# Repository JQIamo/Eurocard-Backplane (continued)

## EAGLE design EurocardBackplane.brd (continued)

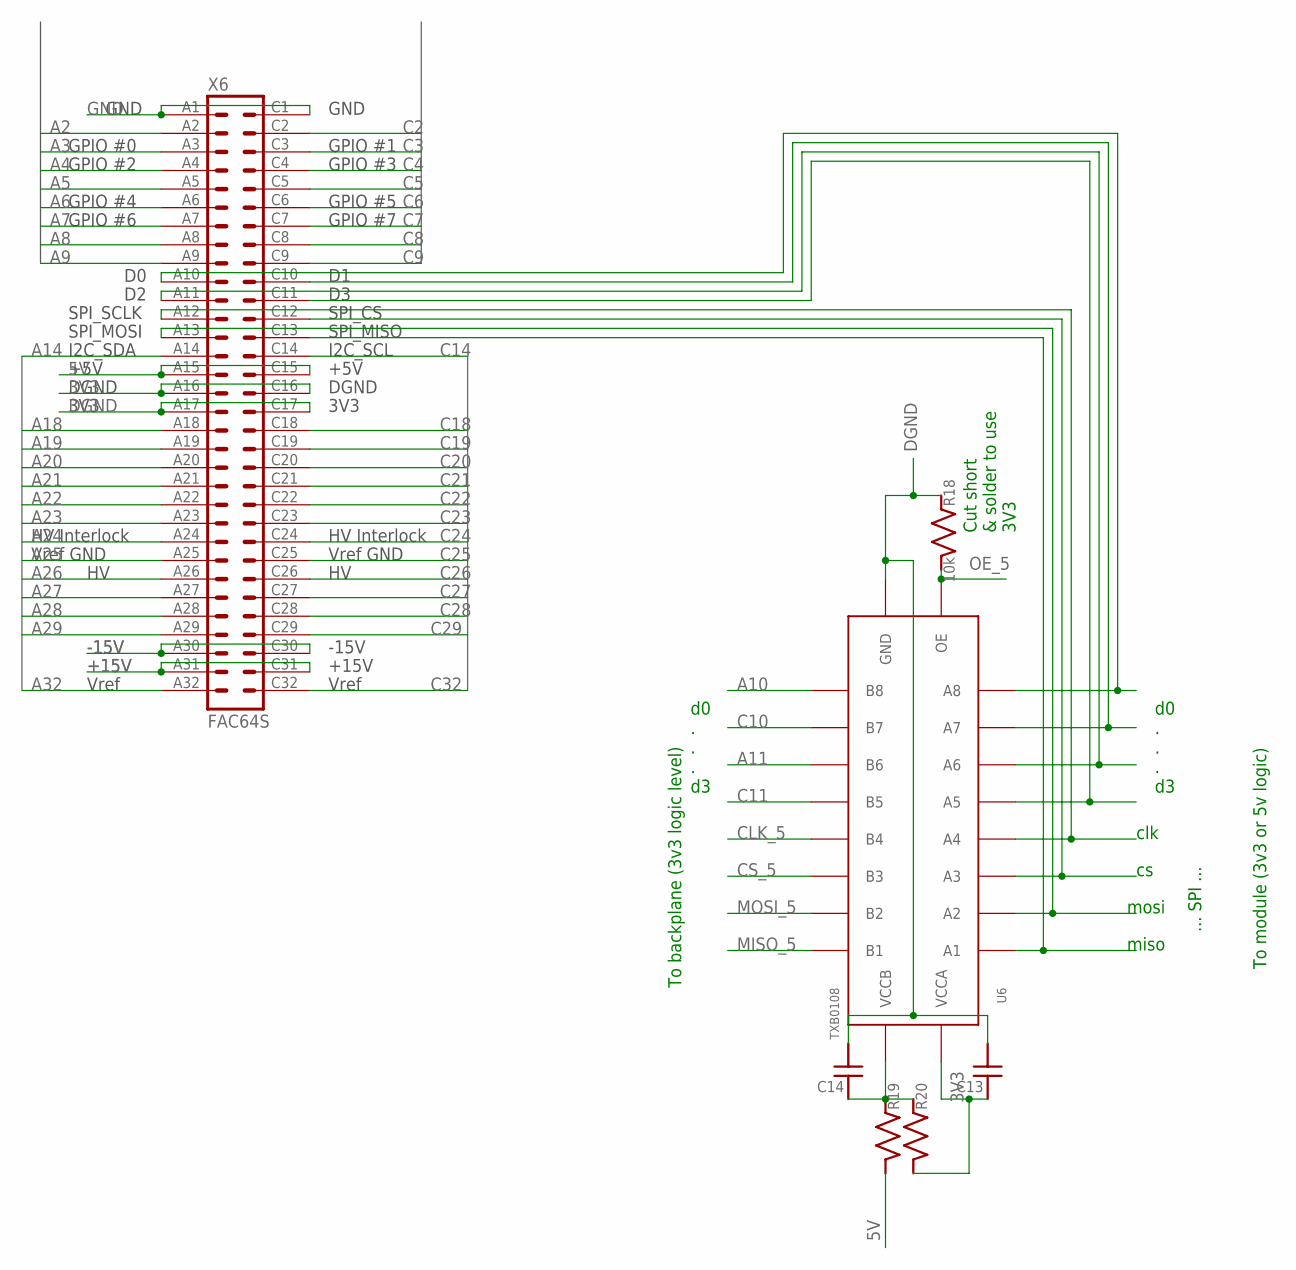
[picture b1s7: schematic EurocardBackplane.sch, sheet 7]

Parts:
C13, C14: C_MLCC_SMDCMLCC_0603; C_MLCC_0603
R18: 10k; R_0603
R19, R20: R_SMDR0603; R_0603
U6: TXB0108; TSSOP20
X6: FAC64S

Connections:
3V3: C13.P$1 (1), R20.P$2 (2), U6.2 (VCCA), X6.A16, X6.C16; also elsewhere on the board
5V: R19.P$2 (2), X6.A15, X6.C15; also elsewhere on the board
+15V: X6.A31, X6.C31; also elsewhere on the board
-15V: X6.A30, X6.C30; also elsewhere on the board
A2: X6.A2; also elsewhere on the board
A3: X6.A3; also elsewhere on the board
A4: X6.A4; also elsewhere on the board
A5: X6.A5; also elsewhere on the board
A6: X6.A6; also elsewhere on the board
A7: X6.A7; also elsewhere on the board
A8: X6.A8; also elsewhere on the board
A9: X6.A9; also elsewhere on the board
A10: U6.12 (B8); also elsewhere on the board
A11: U6.14 (B6); also elsewhere on the board
A14: X6.A14; also elsewhere on the board
A18: X6.A18; also elsewhere on the board
A19: X6.A19; also elsewhere on the board
A20: X6.A20; also elsewhere on the board
A21: X6.A21; also elsewhere on the board
A22: X6.A22; also elsewhere on the board
A23: X6.A23; also elsewhere on the board
A24: X6.A24; also elsewhere on the board
A25: X6.A25; also elsewhere on the board
A26: X6.A26; also elsewhere on the board
A27: X6.A27; also elsewhere on the board
A28: X6.A28; also elsewhere on the board
A29: X6.A29; also elsewhere on the board
A32: X6.A32; also elsewhere on the board
C2: X6.C2; also elsewhere on the board
C3: X6.C3; also elsewhere on the board
C4: X6.C4; also elsewhere on the board
C5: X6.C5; also elsewhere on the board
C6: X6.C6; also elsewhere on the board
C7: X6.C7; also elsewhere on the board
C8: X6.C8; also elsewhere on the board
C9: X6.C9; also elsewhere on the board
C10: U6.13 (B7); also elsewhere on the board
C11: U6.15 (B5); also elsewhere on the board
C14: X6.C14; also elsewhere on the board
C18: X6.C18; also elsewhere on the board
C19: X6.C19; also elsewhere on the board
C20: X6.C20; also elsewhere on the board
C21: X6.C21; also elsewhere on the board
C22: X6.C22; also elsewhere on the board
C23: X6.C23; also elsewhere on the board
C24: X6.C24; also elsewhere on the board
C25: X6.C25; also elsewhere on the board
C26: X6.C26; also elsewhere on the board
C27: X6.C27; also elsewhere on the board
C28: X6.C28; also elsewhere on the board
C29: X6.C29; also elsewhere on the board
C32: X6.C32; also elsewhere on the board
CLK_5: U6.16 (B4); also elsewhere on the board
CS_5: U6.17 (B3); also elsewhere on the board
DGND: C13.P$2 (2), C14.P$2 (2), R18.P$1 (1), U6.11 (GND), X6.A17, X6.C17; also elsewhere on the board
GND: X6.A1, X6.C1; also elsewhere on the board
MISO_5: U6.20 (B1); also elsewhere on the board
MOSI_5: U6.18 (B2); also elsewhere on the board
unnamed: U6.9 (A8), X6.A10
unnamed: U6.8 (A7), X6.C10
unnamed: U6.7 (A6), X6.A11
unnamed: U6.6 (A5), X6.C11
unnamed: U6.5 (A4), X6.A12
unnamed: U6.4 (A3), X6.C12
unnamed: U6.3 (A2), X6.A13
unnamed: U6.1 (A1), X6.C13
unnamed: C14.P$1 (1), R19.P$1 (1), R20.P$1 (1), U6.19 (VCCB)
OE_5: R18.P$2 (2), U6.10 (OE)

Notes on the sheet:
d0 . . . d3
To backplane (3v3 logic level)
To module (3v3 or 5v logic)
clk
mosi
miso
... SPI ...
Cut short & solder to use 3V3

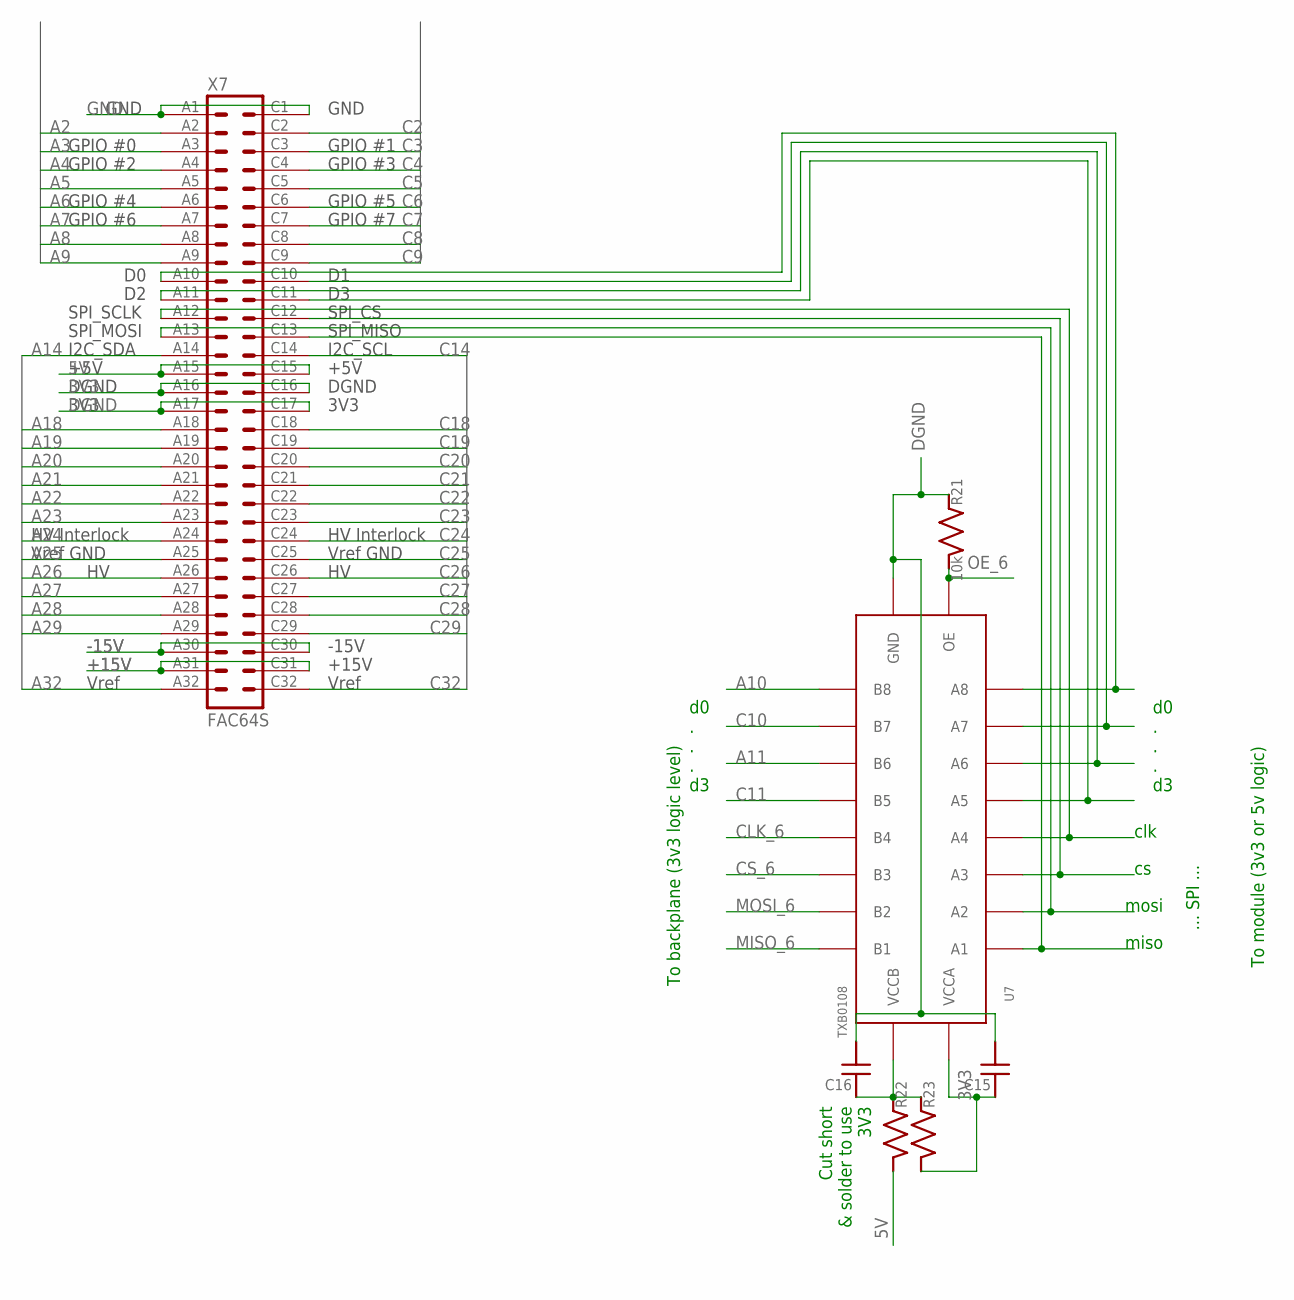
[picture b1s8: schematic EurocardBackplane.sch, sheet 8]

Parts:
C15, C16: C_MLCC_SMDCMLCC_0603; C_MLCC_0603
R21: 10k; R_0603
R22, R23: R_SMDR0603; R_0603
U7: TXB0108; TSSOP20
X7: FAC64S

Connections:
3V3: C15.P$1 (1), R23.P$2 (2), U7.2 (VCCA), X7.A16, X7.C16; also elsewhere on the board
5V: R22.P$2 (2), X7.A15, X7.C15; also elsewhere on the board
+15V: X7.A31, X7.C31; also elsewhere on the board
-15V: X7.A30, X7.C30; also elsewhere on the board
A2: X7.A2; also elsewhere on the board
A3: X7.A3; also elsewhere on the board
A4: X7.A4; also elsewhere on the board
A5: X7.A5; also elsewhere on the board
A6: X7.A6; also elsewhere on the board
A7: X7.A7; also elsewhere on the board
A8: X7.A8; also elsewhere on the board
A9: X7.A9; also elsewhere on the board
A10: U7.12 (B8); also elsewhere on the board
A11: U7.14 (B6); also elsewhere on the board
A14: X7.A14; also elsewhere on the board
A18: X7.A18; also elsewhere on the board
A19: X7.A19; also elsewhere on the board
A20: X7.A20; also elsewhere on the board
A21: X7.A21; also elsewhere on the board
A22: X7.A22; also elsewhere on the board
A23: X7.A23; also elsewhere on the board
A24: X7.A24; also elsewhere on the board
A25: X7.A25; also elsewhere on the board
A26: X7.A26; also elsewhere on the board
A27: X7.A27; also elsewhere on the board
A28: X7.A28; also elsewhere on the board
A29: X7.A29; also elsewhere on the board
A32: X7.A32; also elsewhere on the board
C2: X7.C2; also elsewhere on the board
C3: X7.C3; also elsewhere on the board
C4: X7.C4; also elsewhere on the board
C5: X7.C5; also elsewhere on the board
C6: X7.C6; also elsewhere on the board
C7: X7.C7; also elsewhere on the board
C8: X7.C8; also elsewhere on the board
C9: X7.C9; also elsewhere on the board
C10: U7.13 (B7); also elsewhere on the board
C11: U7.15 (B5); also elsewhere on the board
C14: X7.C14; also elsewhere on the board
C18: X7.C18; also elsewhere on the board
C19: X7.C19; also elsewhere on the board
C20: X7.C20; also elsewhere on the board
C21: X7.C21; also elsewhere on the board
C22: X7.C22; also elsewhere on the board
C23: X7.C23; also elsewhere on the board
C24: X7.C24; also elsewhere on the board
C25: X7.C25; also elsewhere on the board
C26: X7.C26; also elsewhere on the board
C27: X7.C27; also elsewhere on the board
C28: X7.C28; also elsewhere on the board
C29: X7.C29; also elsewhere on the board
C32: X7.C32; also elsewhere on the board
CLK_6: U7.16 (B4); also elsewhere on the board
CS_6: U7.17 (B3); also elsewhere on the board
DGND: C15.P$2 (2), C16.P$2 (2), R21.P$1 (1), U7.11 (GND), X7.A17, X7.C17; also elsewhere on the board
GND: X7.A1, X7.C1; also elsewhere on the board
MISO_6: U7.20 (B1); also elsewhere on the board
MOSI_6: U7.18 (B2); also elsewhere on the board
unnamed: U7.9 (A8), X7.A10
unnamed: U7.8 (A7), X7.C10
unnamed: U7.7 (A6), X7.A11
unnamed: U7.6 (A5), X7.C11
unnamed: U7.5 (A4), X7.A12
unnamed: U7.4 (A3), X7.C12
unnamed: U7.3 (A2), X7.A13
unnamed: U7.1 (A1), X7.C13
unnamed: C16.P$1 (1), R22.P$1 (1), R23.P$1 (1), U7.19 (VCCB)
OE_6: R21.P$2 (2), U7.10 (OE)

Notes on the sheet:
d0 . . . d3
To backplane (3v3 logic level)
To module (3v3 or 5v logic)
clk
mosi
miso
... SPI ...
Cut short & solder to use 3V3

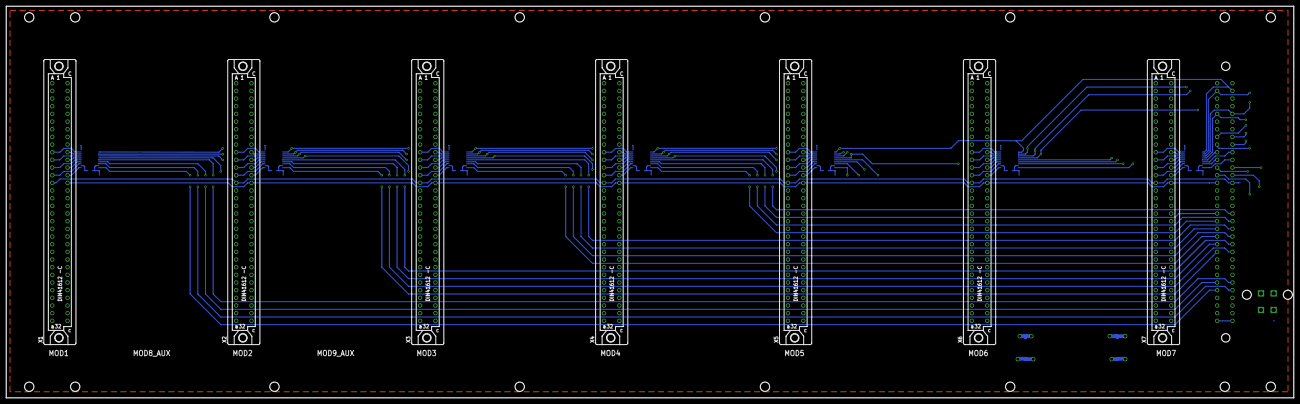
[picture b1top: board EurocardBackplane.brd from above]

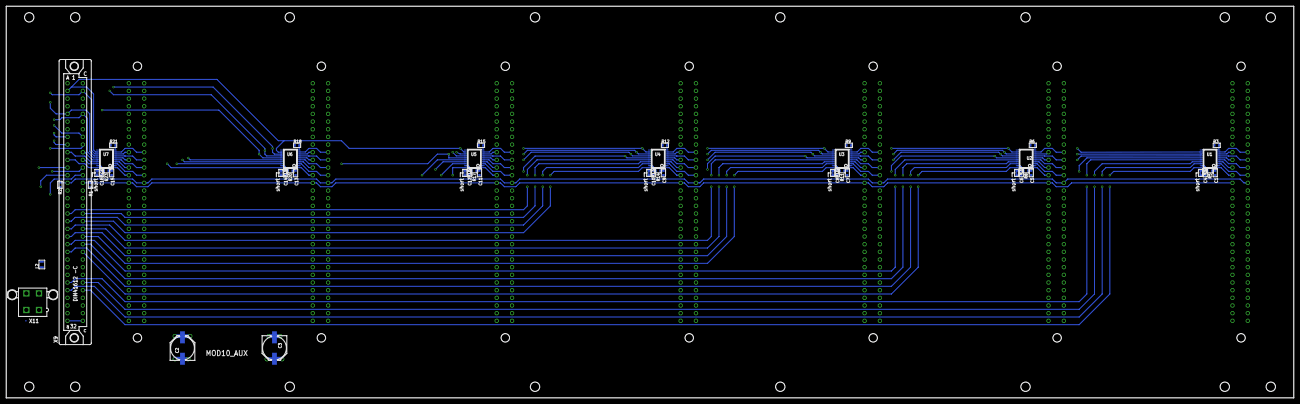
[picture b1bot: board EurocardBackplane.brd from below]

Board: 6 copper layers, 426.7 x 129.8 mm, 59 parts (50 on the bottom side), 153 nets.

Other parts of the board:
U$1, U$4: JQI_LOGO_NEGATIVE-SILKSCREEN
U$3: BACKPLANE

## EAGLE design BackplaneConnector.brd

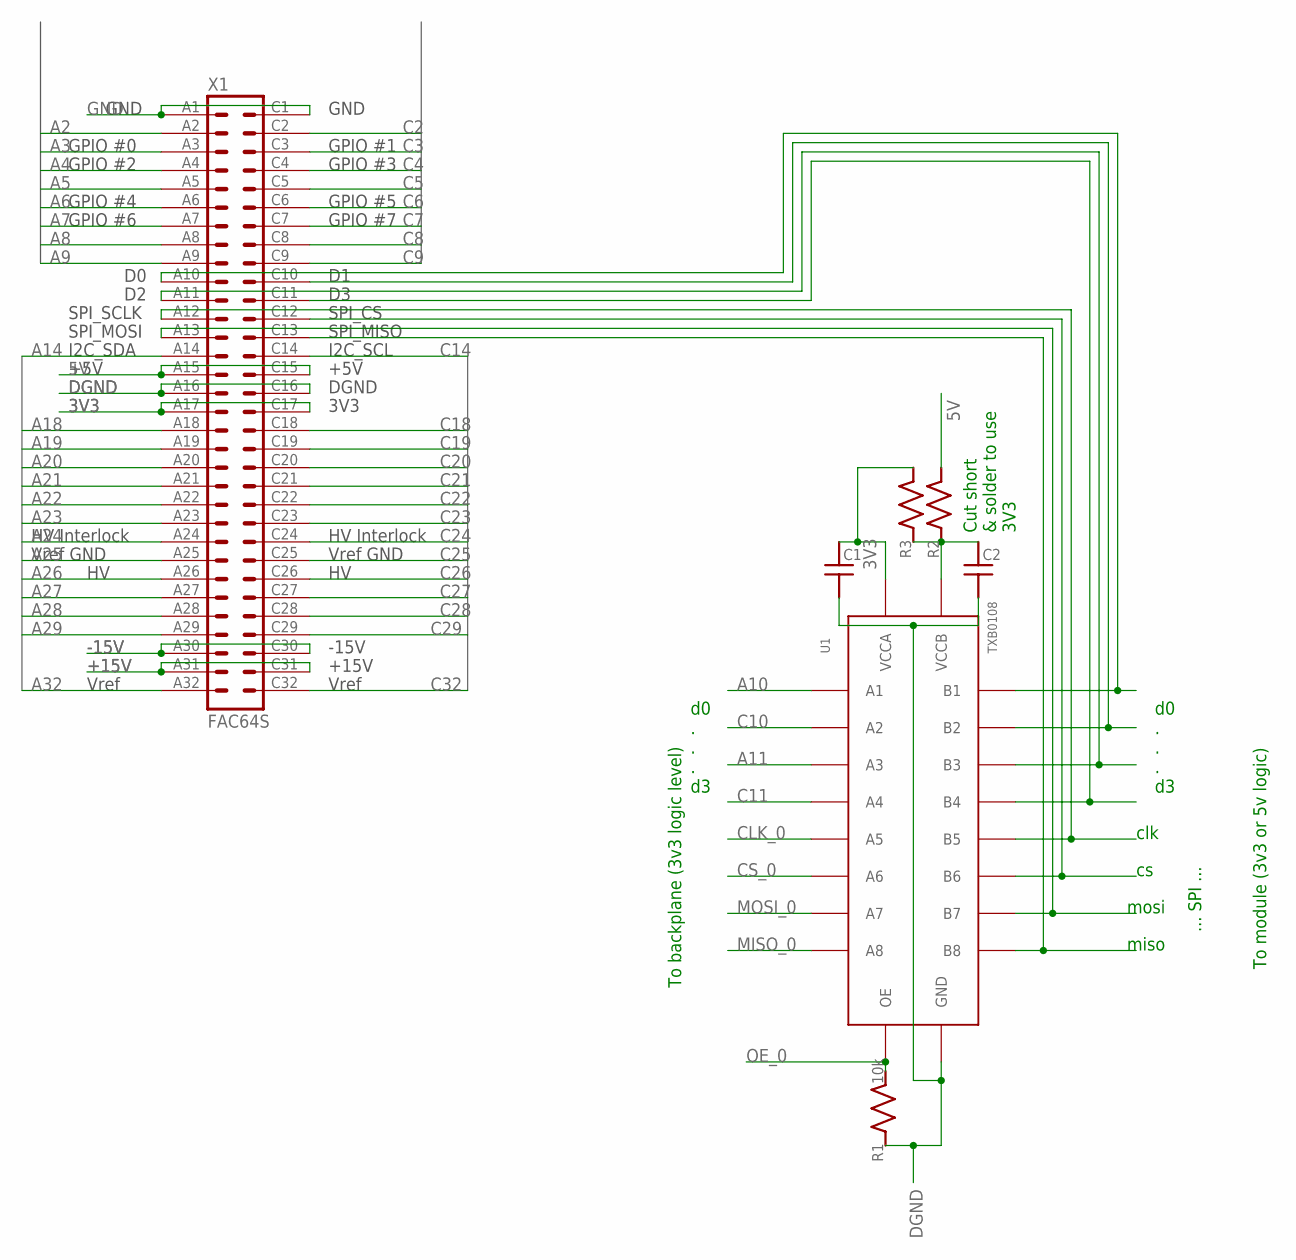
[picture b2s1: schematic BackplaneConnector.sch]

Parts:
C1, C2: C_MLCC_SMDCMLCC_0603; C_MLCC_0603
R1: 10k; R_0603
R2, R3: R_SMDR0603; R_0603
U1: TXB0108; TSSOP20
X1: FAC64S

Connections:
3V3: C1.P$1 (1), R3.P$2 (2), U1.2 (VCCA), X1.A17, X1.C17
5V: R2.P$2 (2), X1.A15, X1.C15
+15V: X1.A31, X1.C31
-15V: X1.A30, X1.C30
A2: X1.A2
A3: X1.A3
A4: X1.A4
A5: X1.A5
A6: X1.A6
A7: X1.A7
A8: X1.A8
A9: X1.A9
A10: U1.1 (A1)
A11: U1.4 (A3)
A14: X1.A14
A18: X1.A18
A19: X1.A19
A20: X1.A20
A21: X1.A21
A22: X1.A22
A23: X1.A23
A24: X1.A24
A25: X1.A25
A26: X1.A26
A27: X1.A27
A28: X1.A28
A29: X1.A29
A32: X1.A32
C2: X1.C2
C3: X1.C3
C4: X1.C4
C5: X1.C5
C6: X1.C6
C7: X1.C7
C8: X1.C8
C9: X1.C9
C10: U1.3 (A2)
C11: U1.5 (A4)
C14: X1.C14
C18: X1.C18
C19: X1.C19
C20: X1.C20
C21: X1.C21
C22: X1.C22
C23: X1.C23
C24: X1.C24
C25: X1.C25
C26: X1.C26
C27: X1.C27
C28: X1.C28
C29: X1.C29
C32: X1.C32
CLK_0: U1.6 (A5)
CS_0: U1.7 (A6)
DGND: C1.P$2 (2), C2.P$2 (2), R1.P$1 (1), U1.11 (GND), X1.A16, X1.C16
GND: X1.A1, X1.C1
MISO_0: U1.9 (A8)
MOSI_0: U1.8 (A7)
unnamed: U1.20 (B1), X1.A10
unnamed: U1.18 (B2), X1.C10
unnamed: U1.17 (B3), X1.A11
unnamed: U1.16 (B4), X1.C11
unnamed: U1.15 (B5), X1.A12
unnamed: U1.14 (B6), X1.C12
unnamed: U1.13 (B7), X1.A13
unnamed: U1.12 (B8), X1.C13
unnamed: C2.P$1 (1), R2.P$1 (1), R3.P$1 (1), U1.19 (VCCB)
OE_0: R1.P$2 (2), U1.10 (OE)

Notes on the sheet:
d0 . . . d3
To backplane (3v3 logic level)
To module (3v3 or 5v logic)
clk
mosi
miso
... SPI ...
Cut short & solder to use 3V3

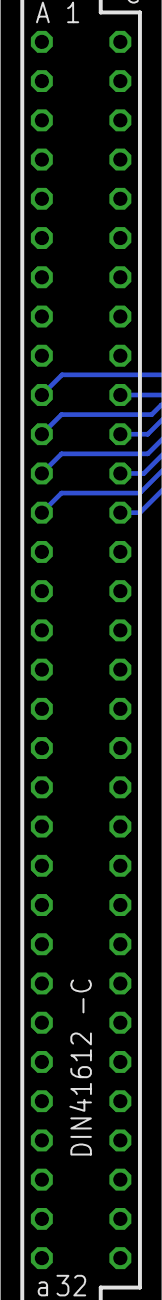
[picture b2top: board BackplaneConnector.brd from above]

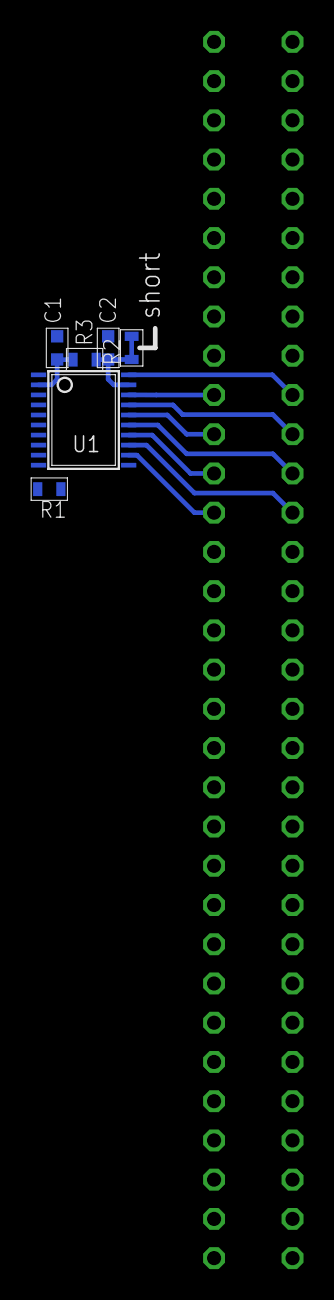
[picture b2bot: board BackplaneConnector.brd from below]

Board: 6 copper layers, 7 parts (6 on the bottom side), 16 nets.

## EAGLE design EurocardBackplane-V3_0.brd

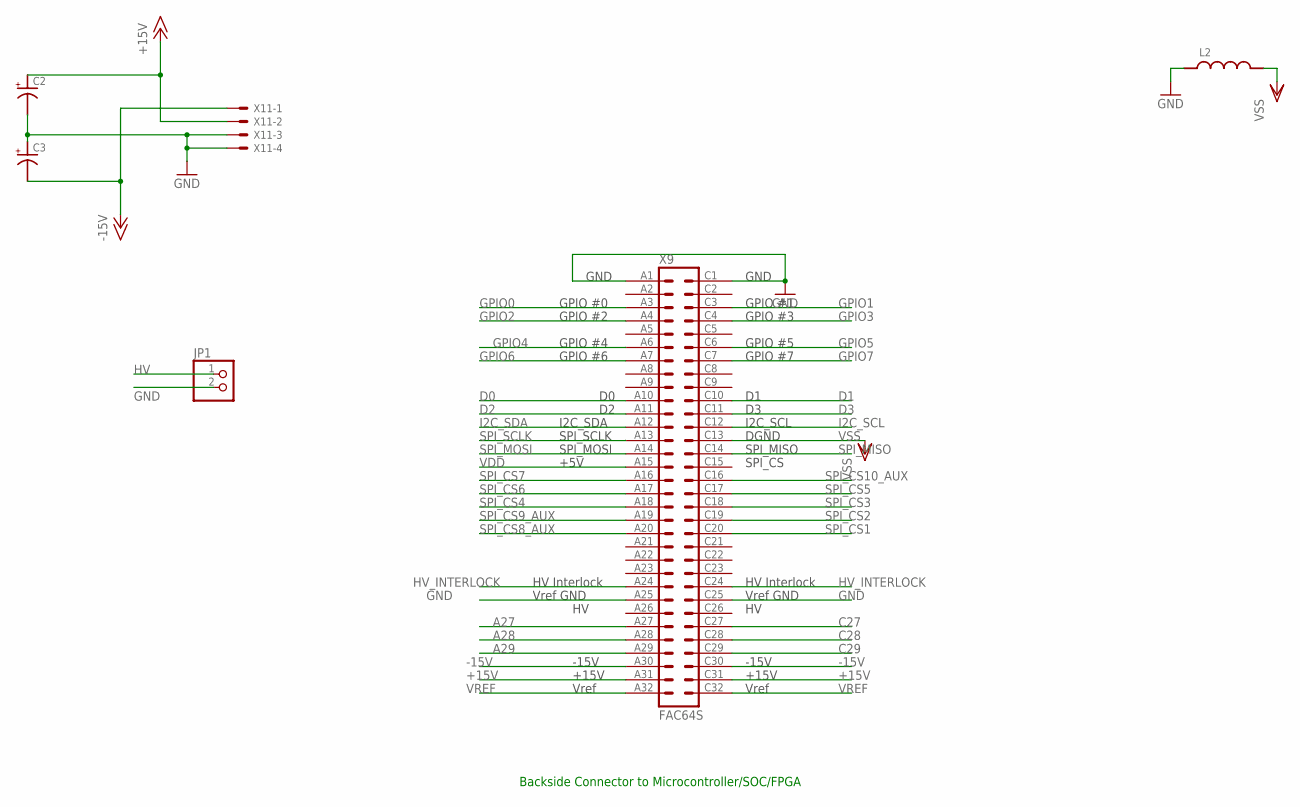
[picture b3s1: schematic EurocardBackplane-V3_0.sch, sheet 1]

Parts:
C2, C3: C_POL_SMDF; PANASONIC_F
JP1: PINHD-1X2; 1X02
L2: L_FERRITE_SMDLFERRITE_0805; R_0805
X9: FAC64S
X11: 5566-4

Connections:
+15V: C2.+, X9.A31, X9.C31, X11.2; also elsewhere on the board
-15V: C3.-, X9.A30, X9.C30, X11.1; also elsewhere on the board
A27: X9.A27; also elsewhere on the board
A28: X9.A28; also elsewhere on the board
A29: X9.A29; also elsewhere on the board
C27: X9.C27; also elsewhere on the board
C28: X9.C28; also elsewhere on the board
C29: X9.C29; also elsewhere on the board
D0: X9.A10; also elsewhere on the board
D1: X9.C10; also elsewhere on the board
D2: X9.A11; also elsewhere on the board
D3: X9.C11; also elsewhere on the board
GND: C2.-, C3.+, JP1.2, L2.P$1 (1), X9.A1, X9.A25, X9.C1, X9.C25, X11.3, X11.4; also elsewhere on the board
GPIO0: X9.A3; also elsewhere on the board
GPIO1: X9.C3; also elsewhere on the board
GPIO2: X9.A4; also elsewhere on the board
GPIO3: X9.C4; also elsewhere on the board
GPIO4: X9.A6; also elsewhere on the board
GPIO5: X9.C6; also elsewhere on the board
GPIO6: X9.A7; also elsewhere on the board
GPIO7: X9.C7; also elsewhere on the board
HV: JP1.1; also elsewhere on the board
HV_INTERLOCK: X9.A24, X9.C24; also elsewhere on the board
I2C_SCL: X9.C12; also elsewhere on the board
I2C_SDA: X9.A12; also elsewhere on the board
SPI_CS1: X9.C20; also elsewhere on the board
SPI_CS2: X9.C19; also elsewhere on the board
SPI_CS3: X9.C18; also elsewhere on the board
SPI_CS4: X9.A18; also elsewhere on the board
SPI_CS5: X9.C17; also elsewhere on the board
SPI_CS6: X9.A17; also elsewhere on the board
SPI_CS7: X9.A16; also elsewhere on the board
SPI_CS8_AUX: X9.A20; also elsewhere on the board
SPI_CS9_AUX: X9.A19; also elsewhere on the board
SPI_CS10_AUX: X9.C16; also elsewhere on the board
SPI_MISO: X9.C14; also elsewhere on the board
SPI_MOSI: X9.A14; also elsewhere on the board
SPI_SCLK: X9.A13; also elsewhere on the board
VDD: X9.A15; also elsewhere on the board
VREF: X9.A32, X9.C32; also elsewhere on the board
VSS: L2.P$2 (2), X9.C13; also elsewhere on the board

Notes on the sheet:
Backside Connector to Microcontroller/SOC/FPGA

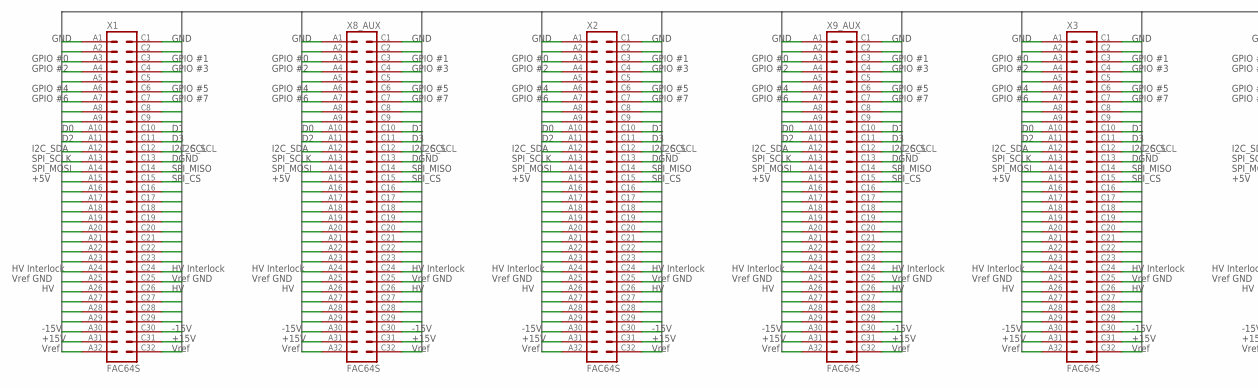
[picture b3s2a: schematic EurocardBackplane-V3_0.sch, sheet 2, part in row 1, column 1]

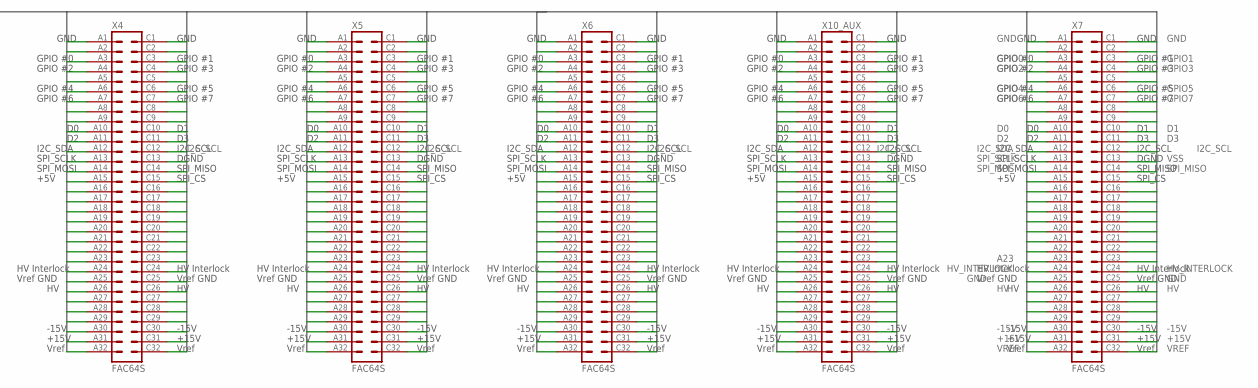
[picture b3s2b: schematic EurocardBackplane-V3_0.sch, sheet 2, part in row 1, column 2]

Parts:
X1, X2, X3, X4, X5, X6, X7, X8_AUX, X9_AUX, X10_AUX: FAC64S

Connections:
+15V: X1.A31, X1.C31, X2.A31, X2.C31, X3.A31, X3.C31, X4.A31, X4.C31, X5.A31, X5.C31, X6.A31, X6.C31, X7.A31, X7.C31, X8_AUX.A31, X8_AUX.C31, X9_AUX.A31, X9_AUX.C31, X10_AUX.A31, X10_AUX.C31; also elsewhere on the board
-15V: X1.A30, X1.C30, X2.A30, X2.C30, X3.A30, X3.C30, X4.A30, X4.C30, X5.A30, X5.C30, X6.A30, X6.C30, X7.A30, X7.C30, X8_AUX.A30, X8_AUX.C30, X9_AUX.A30, X9_AUX.C30, X10_AUX.A30, X10_AUX.C30; also elsewhere on the board
A2: X1.A2, X2.A2, X3.A2, X4.A2, X5.A2, X6.A2, X7.A2, X8_AUX.A2, X9_AUX.A2, X10_AUX.A2
A5: X1.A5, X2.A5, X3.A5, X4.A5, X5.A5, X6.A5, X7.A5, X8_AUX.A5, X9_AUX.A5, X10_AUX.A5
A8: X1.A8, X2.A8, X3.A8, X4.A8, X5.A8, X6.A8, X7.A8, X8_AUX.A8, X9_AUX.A8, X10_AUX.A8
A9: X1.A9, X2.A9, X3.A9, X4.A9, X5.A9, X6.A9, X7.A9, X8_AUX.A9, X9_AUX.A9, X10_AUX.A9
A16: X1.A16, X2.A16, X3.A16, X4.A16, X5.A16, X6.A16, X7.A16, X8_AUX.A16, X9_AUX.A16, X10_AUX.A16
A17: X1.A17, X2.A17, X3.A17, X4.A17, X5.A17, X6.A17, X7.A17, X8_AUX.A17, X9_AUX.A17, X10_AUX.A17
A18: X1.A18, X2.A18, X3.A18, X4.A18, X5.A18, X6.A18, X7.A18, X8_AUX.A18, X9_AUX.A18, X10_AUX.A18
A19: X1.A19, X2.A19, X3.A19, X4.A19, X5.A19, X6.A19, X7.A19, X8_AUX.A19, X9_AUX.A19, X10_AUX.A19
A20: X1.A20, X2.A20, X3.A20, X4.A20, X5.A20, X6.A20, X7.A20, X8_AUX.A20, X9_AUX.A20, X10_AUX.A20
A21: X1.A21, X2.A21, X3.A21, X4.A21, X5.A21, X6.A21, X7.A21, X8_AUX.A21, X9_AUX.A21, X10_AUX.A21
A22: X1.A22, X2.A22, X3.A22, X4.A22, X5.A22, X6.A22, X7.A22, X8_AUX.A22, X9_AUX.A22, X10_AUX.A22
A23: X1.A23, X2.A23, X3.A23, X4.A23, X5.A23, X6.A23, X7.A23, X8_AUX.A23, X9_AUX.A23, X10_AUX.A23
A27: X1.A27, X2.A27, X3.A27, X4.A27, X5.A27, X6.A27, X7.A27, X8_AUX.A27, X9_AUX.A27, X10_AUX.A27; also elsewhere on the board
A28: X1.A28, X2.A28, X3.A28, X4.A28, X5.A28, X6.A28, X7.A28, X8_AUX.A28, X9_AUX.A28, X10_AUX.A28; also elsewhere on the board
A29: X1.A29, X2.A29, X3.A29, X4.A29, X5.A29, X6.A29, X7.A29, X8_AUX.A29, X9_AUX.A29, X10_AUX.A29; also elsewhere on the board
C2: X1.C2, X2.C2, X3.C2, X4.C2, X5.C2, X6.C2, X7.C2, X8_AUX.C2, X9_AUX.C2, X10_AUX.C2
C5: X1.C5, X2.C5, X3.C5, X4.C5, X5.C5, X6.C5, X7.C5, X8_AUX.C5, X9_AUX.C5, X10_AUX.C5
C8: X1.C8, X2.C8, X3.C8, X4.C8, X5.C8, X6.C8, X7.C8, X8_AUX.C8, X9_AUX.C8, X10_AUX.C8
C9: X1.C9, X2.C9, X3.C9, X4.C9, X5.C9, X6.C9, X7.C9, X8_AUX.C9, X9_AUX.C9, X10_AUX.C9
C16: X1.C16, X2.C16, X3.C16, X4.C16, X5.C16, X6.C16, X7.C16, X8_AUX.C16, X9_AUX.C16, X10_AUX.C16
C17: X1.C17, X2.C17, X3.C17, X4.C17, X5.C17, X6.C17, X7.C17, X8_AUX.C17, X9_AUX.C17, X10_AUX.C17
C18: X1.C18, X2.C18, X3.C18, X4.C18, X5.C18, X6.C18, X7.C18, X8_AUX.C18, X9_AUX.C18, X10_AUX.C18
C19: X1.C19, X2.C19, X3.C19, X4.C19, X5.C19, X6.C19, X7.C19, X8_AUX.C19, X9_AUX.C19, X10_AUX.C19
C20: X1.C20, X2.C20, X3.C20, X4.C20, X5.C20, X6.C20, X7.C20, X8_AUX.C20, X9_AUX.C20, X10_AUX.C20
C21: X1.C21, X2.C21, X3.C21, X4.C21, X5.C21, X6.C21, X7.C21, X8_AUX.C21, X9_AUX.C21, X10_AUX.C21
C22: X1.C22, X2.C22, X3.C22, X4.C22, X5.C22, X6.C22, X7.C22, X8_AUX.C22, X9_AUX.C22, X10_AUX.C22
C23: X1.C23, X2.C23, X3.C23, X4.C23, X5.C23, X6.C23, X7.C23, X8_AUX.C23, X9_AUX.C23, X10_AUX.C23
C27: X1.C27, X2.C27, X3.C27, X4.C27, X5.C27, X6.C27, X7.C27, X8_AUX.C27, X9_AUX.C27, X10_AUX.C27; also elsewhere on the board
C28: X1.C28, X2.C28, X3.C28, X4.C28, X5.C28, X6.C28, X7.C28, X8_AUX.C28, X9_AUX.C28, X10_AUX.C28; also elsewhere on the board
C29: X1.C29, X2.C29, X3.C29, X4.C29, X5.C29, X6.C29, X7.C29, X8_AUX.C29, X9_AUX.C29, X10_AUX.C29; also elsewhere on the board
D0: X1.A10, X2.A10, X3.A10, X4.A10, X5.A10, X6.A10, X7.A10, X8_AUX.A10, X9_AUX.A10, X10_AUX.A10; also elsewhere on the board
D1: X1.C10, X2.C10, X3.C10, X4.C10, X5.C10, X6.C10, X7.C10, X8_AUX.C10, X9_AUX.C10, X10_AUX.C10; also elsewhere on the board
D2: X1.A11, X2.A11, X3.A11, X4.A11, X5.A11, X6.A11, X7.A11, X8_AUX.A11, X9_AUX.A11, X10_AUX.A11; also elsewhere on the board
D3: X1.C11, X2.C11, X3.C11, X4.C11, X5.C11, X6.C11, X7.C11, X8_AUX.C11, X9_AUX.C11, X10_AUX.C11; also elsewhere on the board
GND: X1.A1, X1.A25, X1.C1, X1.C25, X2.A1, X2.A25, X2.C1, X2.C25, X3.A1, X3.A25, X3.C1, X3.C25, X4.A1, X4.A25, X4.C1, X4.C25, X5.A1, X5.A25, X5.C1, X5.C25, X6.A1, X6.A25, X6.C1, X6.C25, X7.A1, X7.A25, X7.C1, X7.C25, X8_AUX.A1, X8_AUX.A25, X8_AUX.C1, X8_AUX.C25, X9_AUX.A1, X9_AUX.A25, X9_AUX.C1, X9_AUX.C25, X10_AUX.A1, X10_AUX.A25, X10_AUX.C1, X10_AUX.C25; also elsewhere on the board
GPIO0: X1.A3, X2.A3, X3.A3, X4.A3, X5.A3, X6.A3, X7.A3, X8_AUX.A3, X9_AUX.A3, X10_AUX.A3; also elsewhere on the board
GPIO1: X1.C3, X2.C3, X3.C3, X4.C3, X5.C3, X6.C3, X7.C3, X8_AUX.C3, X9_AUX.C3, X10_AUX.C3; also elsewhere on the board
GPIO2: X1.A4, X2.A4, X3.A4, X4.A4, X5.A4, X6.A4, X7.A4, X8_AUX.A4, X9_AUX.A4, X10_AUX.A4; also elsewhere on the board
GPIO3: X1.C4, X2.C4, X3.C4, X4.C4, X5.C4, X6.C4, X7.C4, X8_AUX.C4, X9_AUX.C4, X10_AUX.C4; also elsewhere on the board
GPIO4: X1.A6, X2.A6, X3.A6, X4.A6, X5.A6, X6.A6, X7.A6, X8_AUX.A6, X9_AUX.A6, X10_AUX.A6; also elsewhere on the board
GPIO5: X1.C6, X2.C6, X3.C6, X4.C6, X5.C6, X6.C6, X7.C6, X8_AUX.C6, X9_AUX.C6, X10_AUX.C6; also elsewhere on the board
GPIO6: X1.A7, X2.A7, X3.A7, X4.A7, X5.A7, X6.A7, X7.A7, X8_AUX.A7, X9_AUX.A7, X10_AUX.A7; also elsewhere on the board
GPIO7: X1.C7, X2.C7, X3.C7, X4.C7, X5.C7, X6.C7, X7.C7, X8_AUX.C7, X9_AUX.C7, X10_AUX.C7; also elsewhere on the board
HV: X1.A26, X1.C26, X2.A26, X2.C26, X3.A26, X3.C26, X4.A26, X4.C26, X5.A26, X5.C26, X6.A26, X6.C26, X7.A26, X7.C26, X8_AUX.A26, X8_AUX.C26, X9_AUX.A26, X9_AUX.C26, X10_AUX.A26, X10_AUX.C26; also elsewhere on the board
HV_INTERLOCK: X1.A24, X1.C24, X2.A24, X2.C24, X3.A24, X3.C24, X4.A24, X4.C24, X5.A24, X5.C24, X6.A24, X6.C24, X7.A24, X7.C24, X8_AUX.A24, X8_AUX.C24, X9_AUX.A24, X9_AUX.C24, X10_AUX.A24, X10_AUX.C24; also elsewhere on the board
I2C_SCL: X1.C12, X2.C12, X3.C12, X4.C12, X5.C12, X6.C12, X7.C12, X8_AUX.C12, X9_AUX.C12, X10_AUX.C12; also elsewhere on the board
I2C_SDA: X1.A12, X2.A12, X3.A12, X4.A12, X5.A12, X6.A12, X7.A12, X8_AUX.A12, X9_AUX.A12, X10_AUX.A12; also elsewhere on the board
SPI_CS1: X1.C15; also elsewhere on the board
SPI_CS2: X2.C15; also elsewhere on the board
SPI_CS3: X3.C15; also elsewhere on the board
SPI_CS4: X4.C15; also elsewhere on the board
SPI_CS5: X5.C15; also elsewhere on the board
SPI_CS6: X6.C15; also elsewhere on the board
SPI_CS7: X7.C15; also elsewhere on the board
SPI_CS8_AUX: X8_AUX.C15; also elsewhere on the board
SPI_CS9_AUX: X9_AUX.C15; also elsewhere on the board
SPI_CS10_AUX: X10_AUX.C15; also elsewhere on the board
SPI_MISO: X1.C14, X2.C14, X3.C14, X4.C14, X5.C14, X6.C14, X7.C14, X8_AUX.C14, X9_AUX.C14, X10_AUX.C14; also elsewhere on the board
SPI_MOSI: X1.A14, X2.A14, X3.A14, X4.A14, X5.A14, X6.A14, X7.A14, X8_AUX.A14, X9_AUX.A14, X10_AUX.A14; also elsewhere on the board
SPI_SCLK: X1.A13, X2.A13, X3.A13, X4.A13, X5.A13, X6.A13, X7.A13, X8_AUX.A13, X9_AUX.A13, X10_AUX.A13; also elsewhere on the board
VDD: X1.A15, X2.A15, X3.A15, X4.A15, X5.A15, X6.A15, X7.A15, X8_AUX.A15, X9_AUX.A15, X10_AUX.A15; also elsewhere on the board
VREF: X1.A32, X1.C32, X2.A32, X2.C32, X3.A32, X3.C32, X4.A32, X4.C32, X5.A32, X5.C32, X6.A32, X6.C32, X7.A32, X7.C32, X8_AUX.A32, X8_AUX.C32, X9_AUX.A32, X9_AUX.C32, X10_AUX.A32, X10_AUX.C32; also elsewhere on the board
VSS: X1.C13, X2.C13, X3.C13, X4.C13, X5.C13, X6.C13, X7.C13, X8_AUX.C13, X9_AUX.C13, X10_AUX.C13; also elsewhere on the board

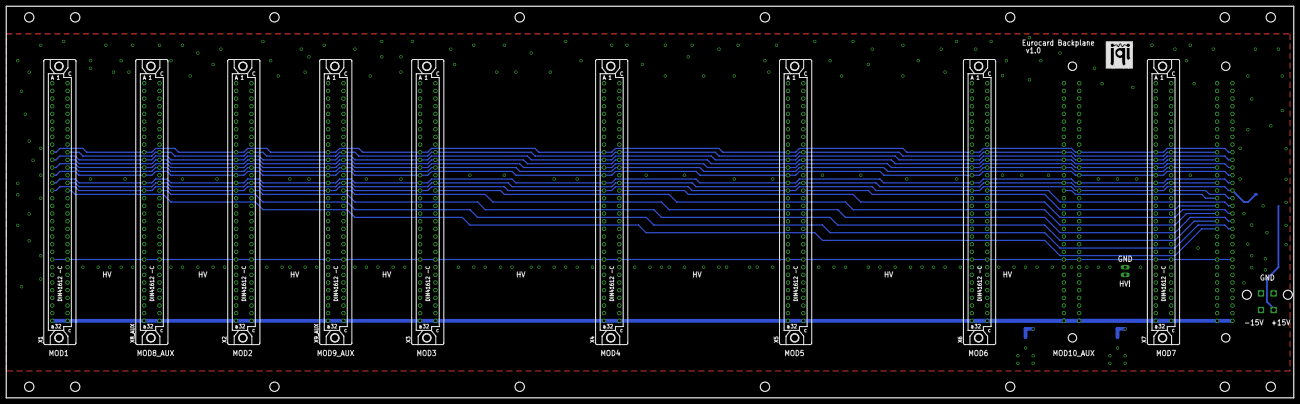
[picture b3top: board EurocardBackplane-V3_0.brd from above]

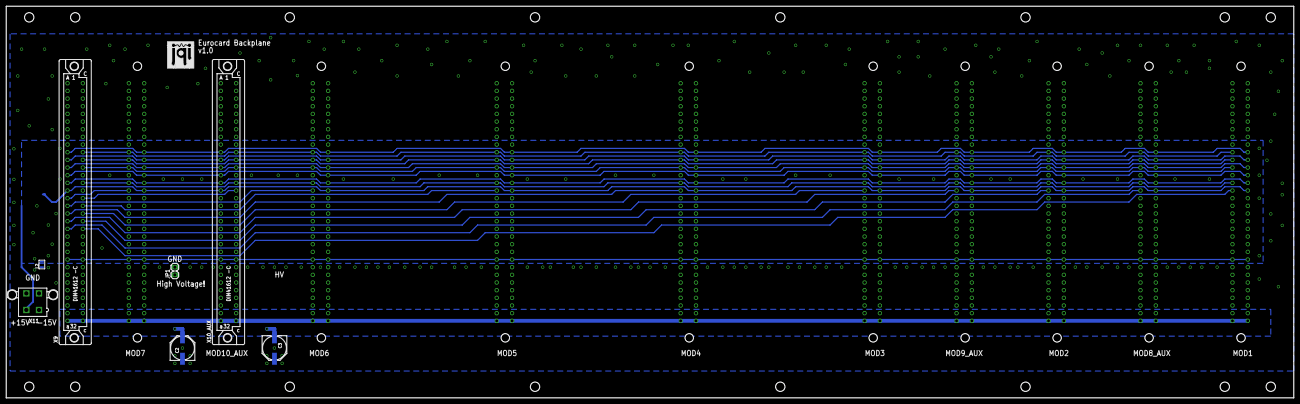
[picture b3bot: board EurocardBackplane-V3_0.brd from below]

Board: 4 copper layers, 426.7 x 129.8 mm, 19 parts (8 on the bottom side), 65 nets.

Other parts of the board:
U$1, U$4: JQI_LOGO_NEGATIVE-SILKSCREEN
U$3: BACKPLANE
